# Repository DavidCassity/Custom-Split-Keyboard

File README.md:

# The Zesty
 Custom Split Keyboard using Ergogen and KiCAD

FUTURE ITERATION:
- Include a double-wide key underneath the middle and index columns
- ~~Make the on off switch connect VCC to RAW since I don't have any idle power draw components~~
- ~~Remap nets to more intuitive pins to decrease routing hell and vias~~
- order new pcbs (once above are complete)
- buy another button and switch

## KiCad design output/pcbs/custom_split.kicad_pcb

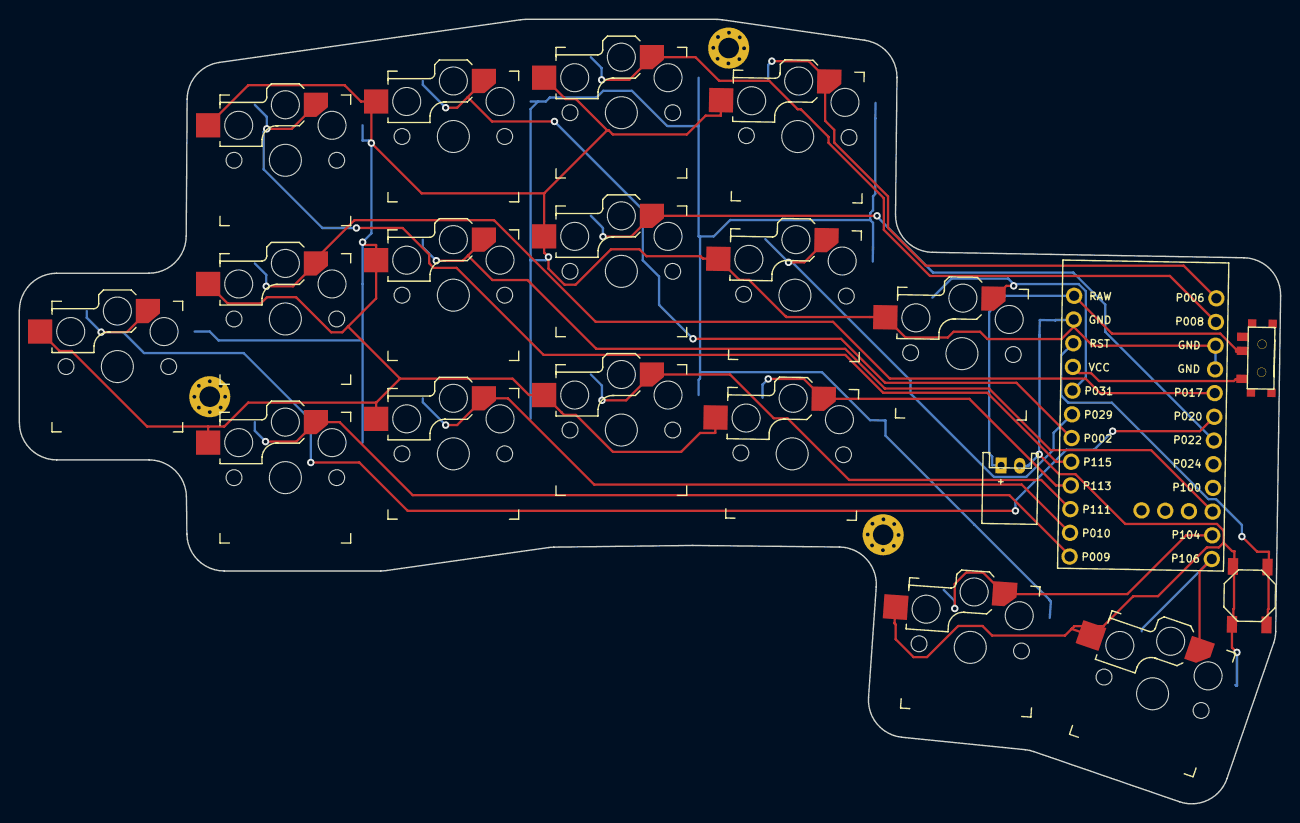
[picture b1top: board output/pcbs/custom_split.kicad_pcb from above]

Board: 2 copper layers, 135.1 x 84.0 mm, 23 parts (0 on the bottom side), 20 nets.

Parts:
B1: SW_TACT_ALPS_SKQGABE010
JST1: JST_PH_S2B-PH-K_02x2.00mm_Angled
MCU1: ProMicro
S1, S2, S3, S4, S5, S6, S7, S8, S9, S10, S11, S12, S13, S14, S15, S16: PG1350
T1: SPDT_C128955
_1, _2, _3: MountingHole_2.2mm_M2_Pad_Via

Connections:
GND: B1.1, JST1.2, MCU1.2, MCU1.15, MCU1.16, S1.2, S2.2, S3.2, S4.2, S5.2, S6.2, S7.2, S8.2, S9.2, S10.2, S11.2, S12.2, S13.2, S14.2, S15.2, S16.2
P002: MCU1.7, S7.1
P006: MCU1.13, S13.1
P008: MCU1.14, S10.1
P009: MCU1.12, S2.1
P010: MCU1.11, S5.1
P011: MCU1.22, S6.1
P017: MCU1.17, S3.1
P020: MCU1.18, S1.1
P022: MCU1.19, S9.1
P029: MCU1.6, S12.1
P031: MCU1.5, S14.1
P104: MCU1.23, S15.1
P106: MCU1.24, S16.1
P111: MCU1.10, S8.1
P113: MCU1.9, S11.1
P115: MCU1.8, S4.1
RAW: JST1.1, MCU1.1, T1.2
RST: B1.2, MCU1.3
VCC: MCU1.4, T1.1

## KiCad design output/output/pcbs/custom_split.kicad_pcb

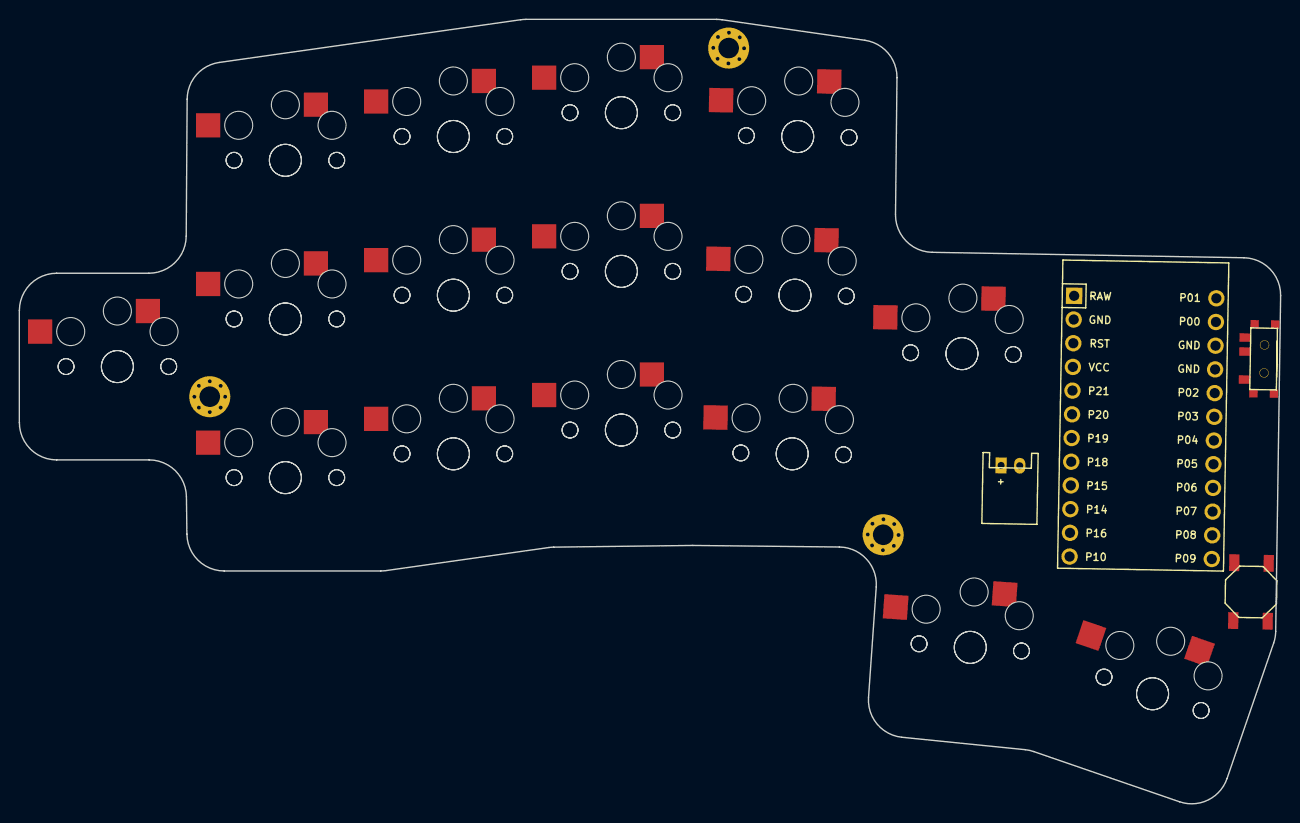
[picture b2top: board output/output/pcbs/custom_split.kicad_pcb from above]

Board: 2 copper layers, 135.1 x 84.0 mm, 39 parts (0 on the bottom side), 20 nets, no tracks yet.

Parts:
B1: SW_TACT_ALPS_SKQGABE010
JST1: JST_PH_S2B-PH-K_02x2.00mm_Angled
MCU1: ProMicro
S1, S2, S3, S4, S5, S6, S7, S8, S9, S10, S11, S12, S13, S14, S15, S16, S17, S18, S19, S20, S21, S22, S23, S24, S25, S26, S27, S28, S29, S30, S31, S32: PG1350
T1: SPDT_C128955
_1, _2, _3: MountingHole_2.2mm_M2_Pad_Via

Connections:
GND: B1.1, JST1.2, MCU1.2, MCU1.15, MCU1.16, S1.2, S2.2, S3.2, S4.2, S5.2, S6.2, S7.2, S8.2, S9.2, S10.2, S11.2, S12.2, S13.2, S14.2, S15.2, S16.2, S17.2, S18.2, S19.2, S20.2, S21.2, S22.2, S23.2, S24.2, S25.2, S26.2, S27.2, S28.2, S29.2, S30.2, S31.2, S32.2, T1.1
P0: MCU1.14, S7.1, S23.1
P1: MCU1.13, S10.1, S26.1
P2: MCU1.17, S4.1, S20.1
P3: MCU1.18, S6.1, S22.1
P4: MCU1.19, S3.1, S19.1
P5: MCU1.20, S1.1, S17.1
P8: MCU1.23, S5.1, S21.1
P9: MCU1.24, S2.1, S18.1
P10: MCU1.12, S9.1, S25.1
P14: MCU1.10, S13.1, S29.1
P15: MCU1.9, S12.1, S28.1
P16: MCU1.11, S8.1, S24.1
P18: MCU1.8, S11.1, S27.1
P19: MCU1.7, S14.1, S30.1
P20: MCU1.6, S15.1, S31.1
P21: MCU1.5, S16.1, S32.1
RAW: JST1.1, MCU1.1
RST: B1.2, MCU1.3
VCC: MCU1.4, T1.2

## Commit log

2022-12-16 Initialized Project
2022-12-16 Add submodules
2022-12-16 Added Footprint Libraries
2022-12-20 Incorporated Ergogen
2023-09-20 Refactored Files
    I moved all of the new PCB files into my current pcb file which is already attached to my GitHub, allowing me to do a local push so I can clone this repo on my laptop.
2023-09-20 Delete currentErgo.txt
    Deleted because it was not my updated design and it was using v3 syntax
2023-09-20 Placed components where I want them (I think)
2023-09-21 Routed the keeb!
2023-09-21 not actually sure what changed
2023-09-23 A lot happened
    Got all of ben's incompatible js files off of the board in ergogen and it worked. I have to stick with the shitty button oh well. Moved everything ergogen related into the ergowrap folder in order to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
2023-09-23 Placed components, made case
    Placed all of the necessary components on the board. Kept the 4 pad button instead of the 2 pad button. Added mounting holes. Created a case with standoffs to use on the bottom of the left half of th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
2024-02-24 renamed folders to make more sense; mounting holes don't compile properly
2024-02-24 let drew look at it
2024-02-25 changed board constraints
2024-02-26 added new choc footprint
2024-02-26 switched the footprint to one that didn't clip pads; no more errors in kicad
2024-02-26 forgot to save the bp
2024-03-31 added nice!nano footprint and updated the config
2024-04-04 renamed the pins and regenerated the nets
